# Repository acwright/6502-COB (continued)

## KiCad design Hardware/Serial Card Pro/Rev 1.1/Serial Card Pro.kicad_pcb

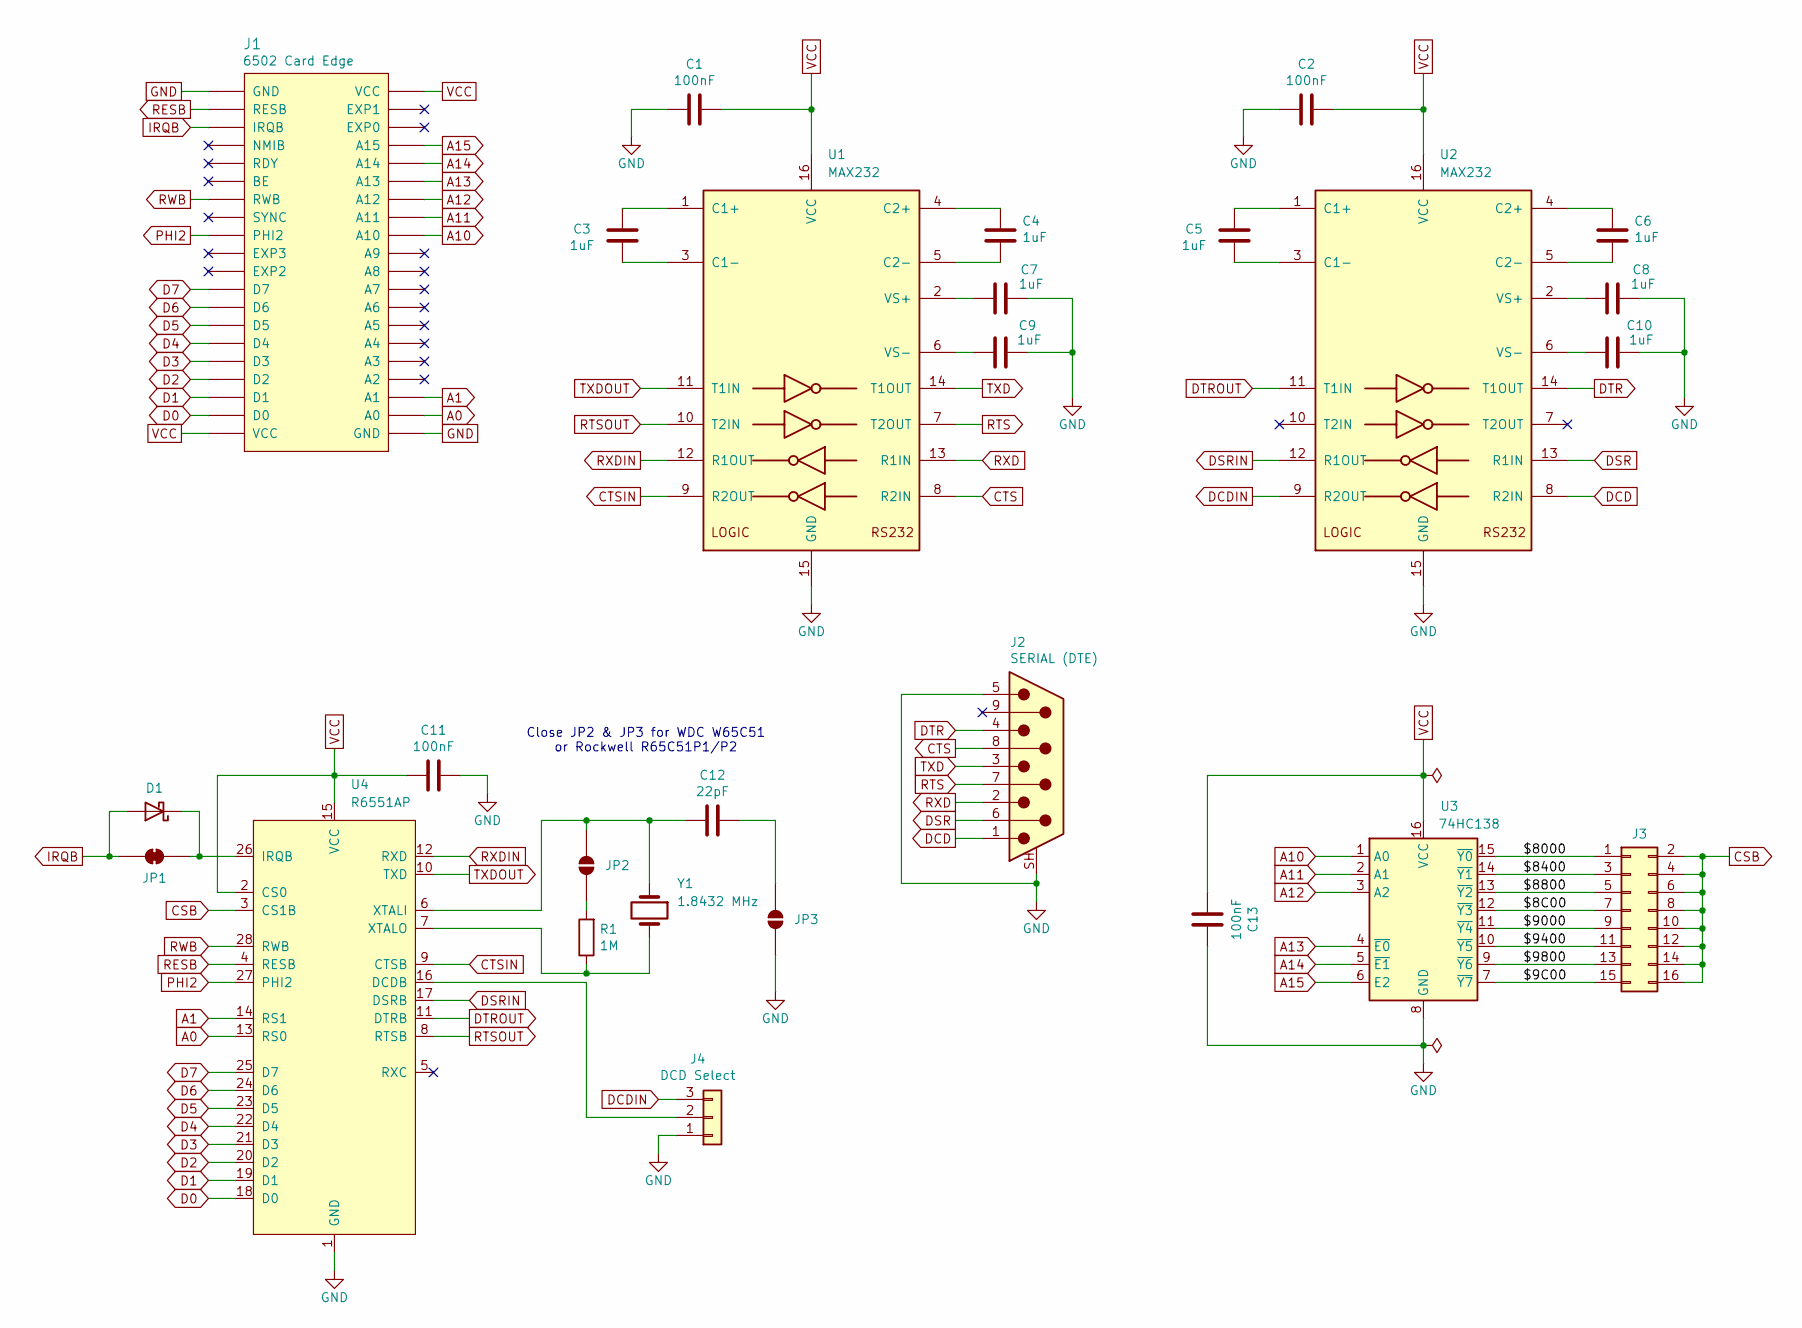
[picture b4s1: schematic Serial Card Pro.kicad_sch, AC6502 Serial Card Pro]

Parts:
C1, C2, C11, C13: 100nF; C_0805_2012Metric; LCSC C49678
C3, C4, C5, C6, C7, C8, C9, C10: 1uF; C_0805_2012Metric; LCSC C28323
C12: 22pF; C_0805_2012Metric; LCSC C1804
D1: BAT85; D_DO-35_SOD27_P7.62mm_Horizontal; Digikey BAT85SCT-ND
J1: 6502 Card Edge
J2: SERIAL (DTE); DSUB-9_Pins_Horizontal_P2.77x2.84mm_EdgePinOffset7.70mm_Hou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; Digikey 609-1481-ND
J3: Conn_02x08_Odd_Even; PinHeader_2x08_P2.54mm_Vertical; Digikey S2011EC-40-ND
J4: DCD Select; PinHeader_1x03_P2.54mm_Vertical; Digikey S1011EC-40-ND
JP1: SolderJumper_2_Bridged; SolderJumper-2_P1.3mm_Bridged_RoundedPad1.0x1.5mm
JP2, JP3: SolderJumper_2_Open; SolderJumper-2_P1.3mm_Open_RoundedPad1.0x1.5mm
R1: 1M; R_0805_2012Metric; LCSC C17514
U1, U2: MAX232; SOIC-16; LCSC C59824
U3: 74HC138; SOIC-16_3.9x9.9mm_P1.27mm; LCSC C5602
U4: R6551AP; DIP-28_W15.24mm_Socket_LongPads
Y1: 1.8432 MHz; Crystal_HC49-U_Vertical; Digikey 535-9009-ND

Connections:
/$8C00: J3.7, U3.12 (~Y3)
/$9C00: J3.15, U3.7 (~Y7)
/$8000: J3.1, U3.15 (~Y0)
/$8400: J3.3, U3.14 (~Y1)
/$8800: J3.5, U3.13 (~Y2)
/$9000: J3.9, U3.11 (~Y4)
/$9400: J3.11, U3.10 (~Y5)
/$9800: J3.13, U3.9 (~Y6)
A0: J1.A0, U4.13 (RS0)
A1: J1.A1, U4.14 (RS1)
A10: J1.A10, U3.1 (A0)
A11: J1.A11, U3.2 (A1)
A12: J1.A12, U3.3 (A2)
A13: J1.A13, U3.4 (~E0)
A14: J1.A14, U3.5 (~E1)
A15: J1.A15, U3.6 (E2)
CSB: J3.2, J3.4, J3.6, J3.8, J3.10, J3.12, J3.14, J3.16, U4.3 (CS1B)
CTS: J2.8, U1.8 (R2IN)
CTSIN: U1.9 (R2OUT), U4.9 (CTSB)
D0: J1.D0, U4.18 (D0)
D1: J1.D1, U4.19 (D1)
D2: J1.D2, U4.20 (D2)
D3: J1.D3, U4.21 (D3)
D4: J1.D4, U4.22 (D4)
D5: J1.D5, U4.23 (D5)
D6: J1.D6, U4.24 (D6)
D7: J1.D7, U4.25 (D7)
DCD: J2.1, U2.8 (R2IN)
DCDIN: J4.3, U2.9 (R2OUT)
DSR: J2.6, U2.13 (R1IN)
DSRIN: U2.12 (R1OUT), U4.17 (DSRB)
DTR: J2.4, U2.14 (T1OUT)
DTROUT: U2.11 (T1IN), U4.11 (DTRB)
GND: C1.1, C2.1, C7.2, C8.2, C9.2, C10.2, C11.2, C13.2, J1.GND, J2.5, J2.SH (PAD), J4.1, JP3.1 (A), U1.15 (GND), U2.15 (GND), U3.8 (GND), U4.1 (GND)
IRQB: D1.2 (A), J1.IRQB, JP1.1 (A)
unnamed: D1.1 (K), JP1.2 (B), U4.26 (IRQB)
unnamed: J4.2, U4.16 (DCDB)
unnamed: JP2.1 (A), R1.2
unnamed: C12.2, JP2.2 (B), U4.6 (XTALI), Y1.1
unnamed: C12.1, JP3.2 (B)
unnamed: C3.1, U1.1 (C1+)
unnamed: C3.2, U1.3 (C1-)
unnamed: C4.1, U1.4 (C2+)
unnamed: C4.2, U1.5 (C2-)
unnamed: C7.1, U1.2 (VS+)
unnamed: C9.1, U1.6 (VS-)
unnamed: C5.1, U2.1 (C1+)
unnamed: C5.2, U2.3 (C1-)
unnamed: C6.1, U2.4 (C2+)
unnamed: C6.2, U2.5 (C2-)
unnamed: C8.1, U2.2 (VS+)
unnamed: C10.1, U2.6 (VS-)
unnamed: R1.1, U4.7 (XTALO), Y1.2
PHI2: J1.PHI2, U4.27 (PHI2)
RESB: J1.RESB, U4.4 (RESB)
RTS: J2.7, U1.7 (T2OUT)
RTSOUT: U1.10 (T2IN), U4.8 (RTSB)
RWB: J1.RWB, U4.28 (RWB)
RXD: J2.2, U1.13 (R1IN)
RXDIN: U1.12 (R1OUT), U4.12 (RXD)
TXD: J2.3, U1.14 (T1OUT)
TXDOUT: U1.11 (T1IN), U4.10 (TXD)
VCC: C1.2, C2.2, C11.1, C13.1, J1.VCC, U1.16 (VCC), U2.16 (VCC), U3.16 (VCC), U4.2 (CS0), U4.15 (VCC)

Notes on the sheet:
Close JP2 & JP3 for WDC W65C51 or Rockwell R65C51P1/P2

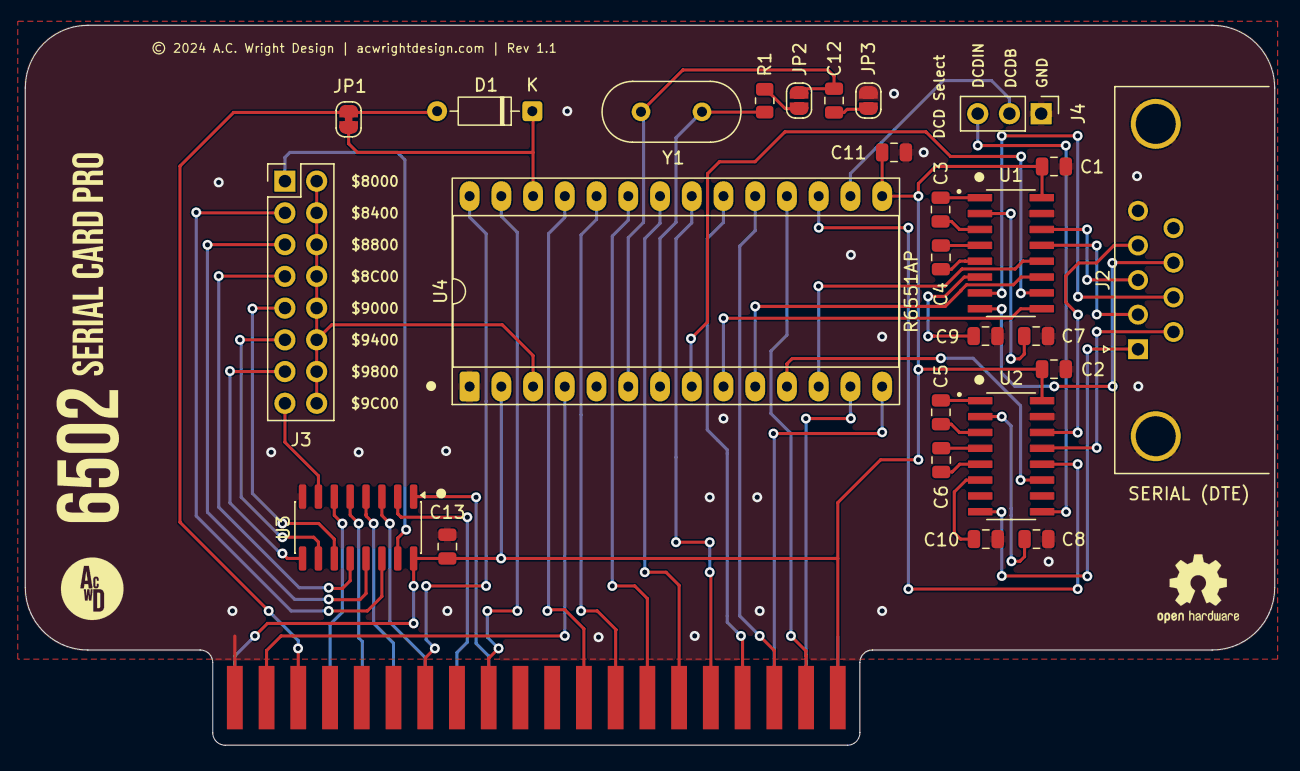
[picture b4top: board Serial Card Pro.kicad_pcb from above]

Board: 2 copper layers, 100.0 x 57.6 mm, 27 parts (0 on the bottom side), 63 nets.

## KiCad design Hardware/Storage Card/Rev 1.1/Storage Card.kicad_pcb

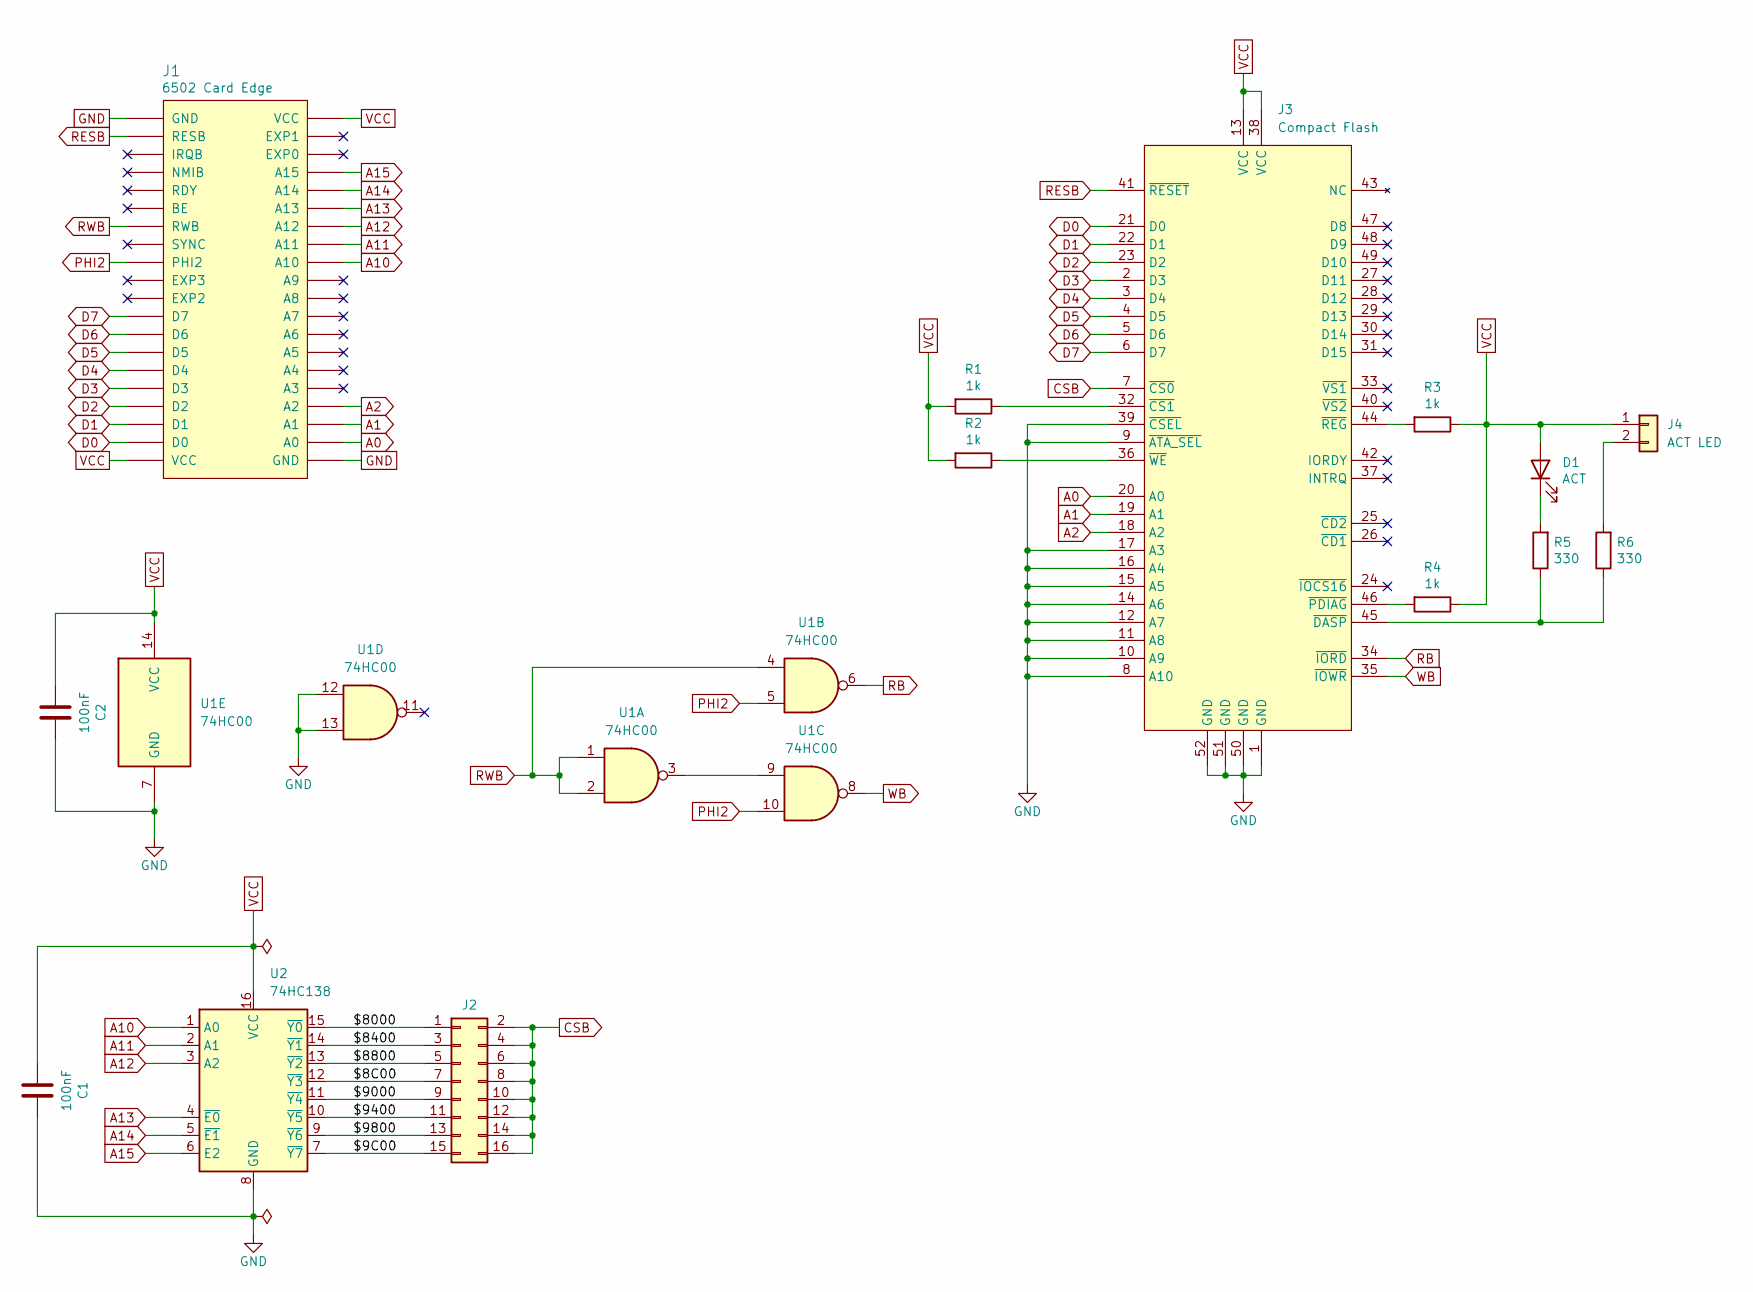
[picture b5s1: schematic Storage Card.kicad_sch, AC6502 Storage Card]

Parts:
C1, C2: 100nF; C_0805_2012Metric; LCSC C49678
D1: ACT; LED_0805_2012Metric; LCSC C2297
J1: 6502 Card Edge
J2: Conn_02x08_Odd_Even; PinHeader_2x08_P2.54mm_Vertical; Digikey S2011EC-40-ND
J3: Compact Flash; CompactFlash Socket Plated Pegs; LCSC C444350
J4: ACT LED; JST_XH_B2B-XH-A_1x02_P2.50mm_Vertical; Digikey 455-B2B-XH-A-ND
R1, R2, R3, R4: 1k; R_0805_2012Metric; LCSC C17513
R5, R6: 330; R_0805_2012Metric; LCSC C17630
U1: 74HC00; SOIC-14_3.9x8.7mm_P1.27mm; LCSC C5586
U2: 74HC138; SOIC-16_3.9x9.9mm_P1.27mm; LCSC C5602

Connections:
/$8C00: J2.7, U2.12 (~Y3)
/$9C00: J2.15, U2.7 (~Y7)
/$8000: J2.1, U2.15 (~Y0)
/$8400: J2.3, U2.14 (~Y1)
/$8800: J2.5, U2.13 (~Y2)
/$9000: J2.9, U2.11 (~Y4)
/$9400: J2.11, U2.10 (~Y5)
/$9800: J2.13, U2.9 (~Y6)
A0: J1.A0, J3.20 (A0)
A1: J1.A1, J3.19 (A1)
A2: J1.A2, J3.18 (A2)
A10: J1.A10, U2.1 (A0)
A11: J1.A11, U2.2 (A1)
A12: J1.A12, U2.3 (A2)
A13: J1.A13, U2.4 (~E0)
A14: J1.A14, U2.5 (~E1)
A15: J1.A15, U2.6 (E2)
CSB: J2.2, J2.4, J2.6, J2.8, J2.10, J2.12, J2.14, J2.16, J3.7 (~CS0)
D0: J1.D0, J3.21 (D0)
D1: J1.D1, J3.22 (D1)
D2: J1.D2, J3.23 (D2)
D3: J1.D3, J3.2 (D3)
D4: J1.D4, J3.3 (D4)
D5: J1.D5, J3.4 (D5)
D6: J1.D6, J3.5 (D6)
D7: J1.D7, J3.6 (D7)
GND: C1.2, C2.2, J1.GND, J3.1 (GND), J3.8 (A10), J3.9 (~ATA_SEL), J3.10 (A9), J3.11 (A8), J3.12 (A7), J3.14 (A6), J3.15 (A5), J3.16 (A4), J3.17 (A3), J3.39 (~CSEL), J3.50 (GND), J3.51 (GND), J3.52 (GND), U1.7 (GND), U1.12, U1.13, U2.8 (GND)
unnamed: D1.1 (K), R5.2
unnamed: J3.32 (~CS1), R1.1
unnamed: J3.45 (~DASP), R5.1, R6.1
unnamed: J3.46 (~PDIAG), R4.2
unnamed: J3.44 (~REG), R3.2
unnamed: J3.36 (~WE), R2.1
unnamed: J4.2, R6.2
unnamed: U1.3, U1.9
PHI2: J1.PHI2, U1.5, U1.10
RB: J3.34 (~IORD), U1.6
RESB: J1.RESB, J3.41 (~RESET)
RWB: J1.RWB, U1.1, U1.2, U1.4
VCC: C1.1, C2.1, D1.2 (A), J1.VCC, J3.13 (VCC), J3.38 (VCC), J4.1, R1.2, R2.2, R3.1, R4.1, U1.14 (VCC), U2.16 (VCC)
WB: J3.35 (~IOWR), U1.8

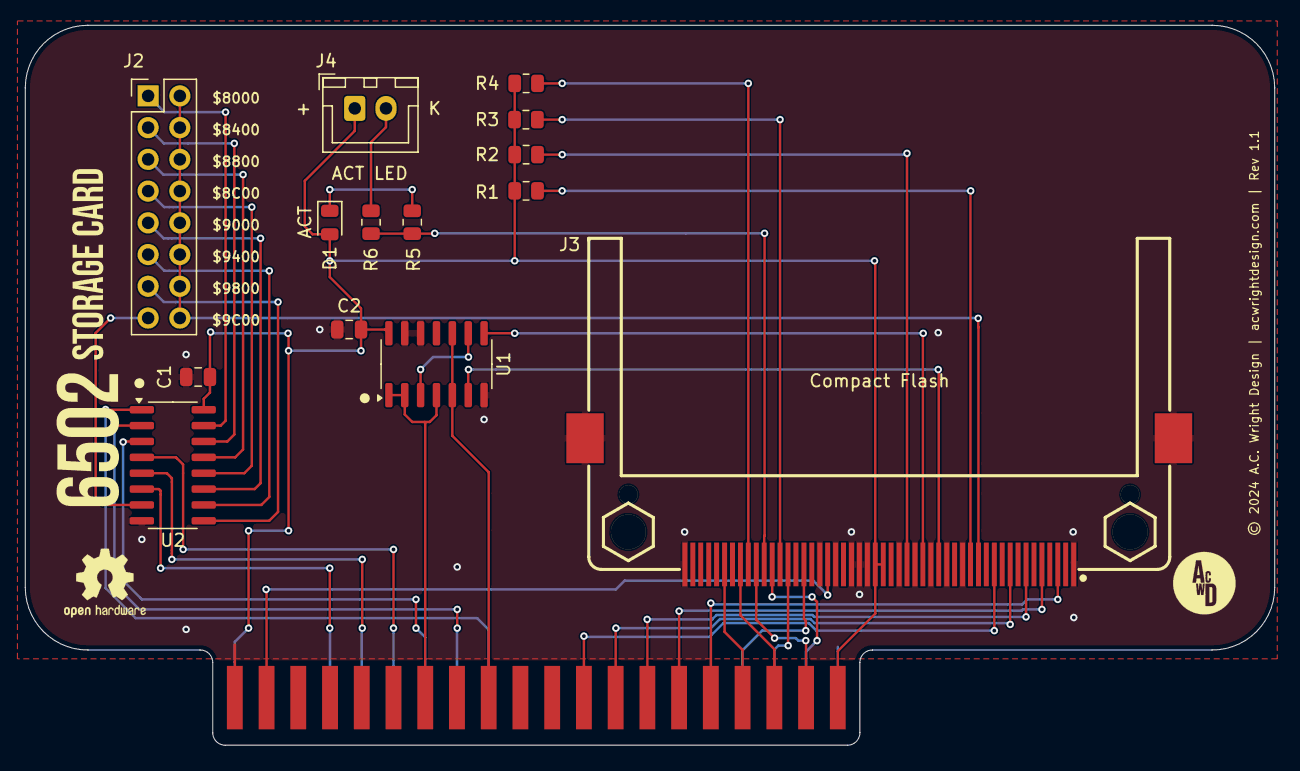
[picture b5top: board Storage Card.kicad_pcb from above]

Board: 2 copper layers, 100.0 x 57.6 mm, 15 parts (0 on the bottom side), 41 nets.

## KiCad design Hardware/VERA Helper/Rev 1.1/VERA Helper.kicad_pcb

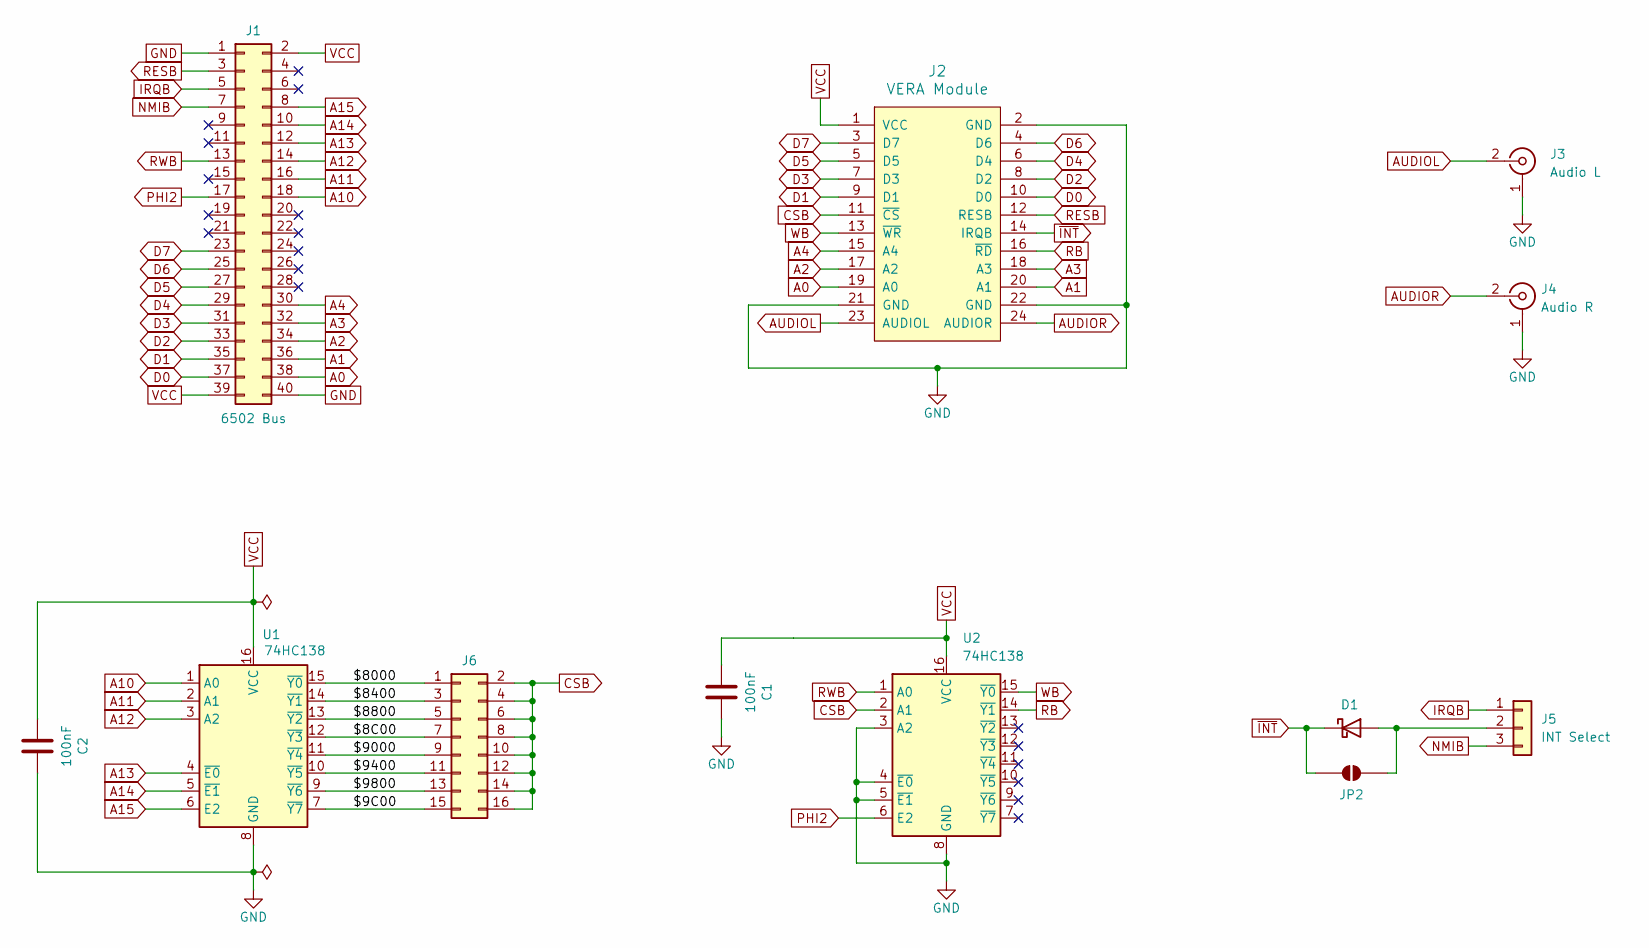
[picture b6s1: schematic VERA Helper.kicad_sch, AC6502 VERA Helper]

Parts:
C1, C2: 100nF; C_Disc_D5.0mm_W2.5mm_P2.50mm; Digikey 478-3187-ND
D1: BAT85; D_DO-35_SOD27_P7.62mm_Horizontal; Digikey BAT85SCT-ND
J1: 6502 Bus; 6502 Bus Connector; Digikey 732-5401-ND
J2: VERA Module; PinHeader_2x12_P2.54mm_Vertical; Digikey S2011EC-40-ND
J3: Audio L; RCA Jack White; Digikey PJRAN1X1U02X-ND
J4: Audio R; RCA Jack White; Digikey PJRAN1X1U03X-ND
J5: INT Select; PinHeader_1x03_P2.54mm_Vertical; Digikey S1011EC-40-ND
J6: Conn_02x08_Odd_Even; PinHeader_2x08_P2.54mm_Vertical; Digikey S2011EC-40-ND
JP2: SolderJumper_2_Open; SolderJumper-2_P1.3mm_Open_RoundedPad1.0x1.5mm
U1, U2: 74HC138; DIP-16_W7.62mm_Socket_LongPads; Digikey 296-1575-5-ND

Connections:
/$8C00: J6.7, U1.12 (~Y3)
/$9C00: J6.15, U1.7 (~Y7)
/$8000: J6.1, U1.15 (~Y0)
/$8400: J6.3, U1.14 (~Y1)
/$8800: J6.5, U1.13 (~Y2)
/$9000: J6.9, U1.11 (~Y4)
/$9400: J6.11, U1.10 (~Y5)
/$9800: J6.13, U1.9 (~Y6)
A0: J1.38, J2.19 (A0)
A1: J1.36, J2.20 (A1)
A2: J1.34, J2.17 (A2)
A3: J1.32, J2.18 (A3)
A4: J1.30, J2.15 (A4)
A10: J1.18, U1.1 (A0)
A11: J1.16, U1.2 (A1)
A12: J1.14, U1.3 (A2)
A13: J1.12, U1.4 (~E0)
A14: J1.10, U1.5 (~E1)
A15: J1.8, U1.6 (E2)
AUDIOL: J2.23 (AUDIOL), J3.2 (In)
AUDIOR: J2.24 (AUDIOR), J4.2 (In)
CSB: J2.11 (~CS), J6.2, J6.4, J6.6, J6.8, J6.10, J6.12, J6.14, J6.16, U2.2 (A1)
D0: J1.37, J2.10 (D0)
D1: J1.35, J2.9 (D1)
D2: J1.33, J2.8 (D2)
D3: J1.31, J2.7 (D3)
D4: J1.29, J2.6 (D4)
D5: J1.27, J2.5 (D5)
D6: J1.25, J2.4 (D6)
D7: J1.23, J2.3 (D7)
GND: C1.2, C2.2, J1.1, J1.40, J2.2 (GND), J2.21 (GND), J2.22 (GND), J3.1 (Ext), J4.1 (Ext), U1.8 (GND), U2.3 (A2), U2.4 (~E0), U2.5 (~E1), U2.8 (GND)
IRQB: J1.5, J5.1
NMIB: J1.7, J5.3
unnamed: D1.2 (A), J5.2, JP2.2 (B)
PHI2: J1.17, U2.6 (E2)
RB: J2.16 (~RD), U2.14 (~Y1)
RESB: J1.3, J2.12 (RESB)
RWB: J1.13, U2.1 (A0)
VCC: C1.1, C2.1, J1.2, J1.39, J2.1 (VCC), U1.16 (VCC), U2.16 (VCC)
WB: J2.13 (~WR), U2.15 (~Y0)
~INT: D1.1 (K), J2.14 (IRQB), JP2.1 (A)

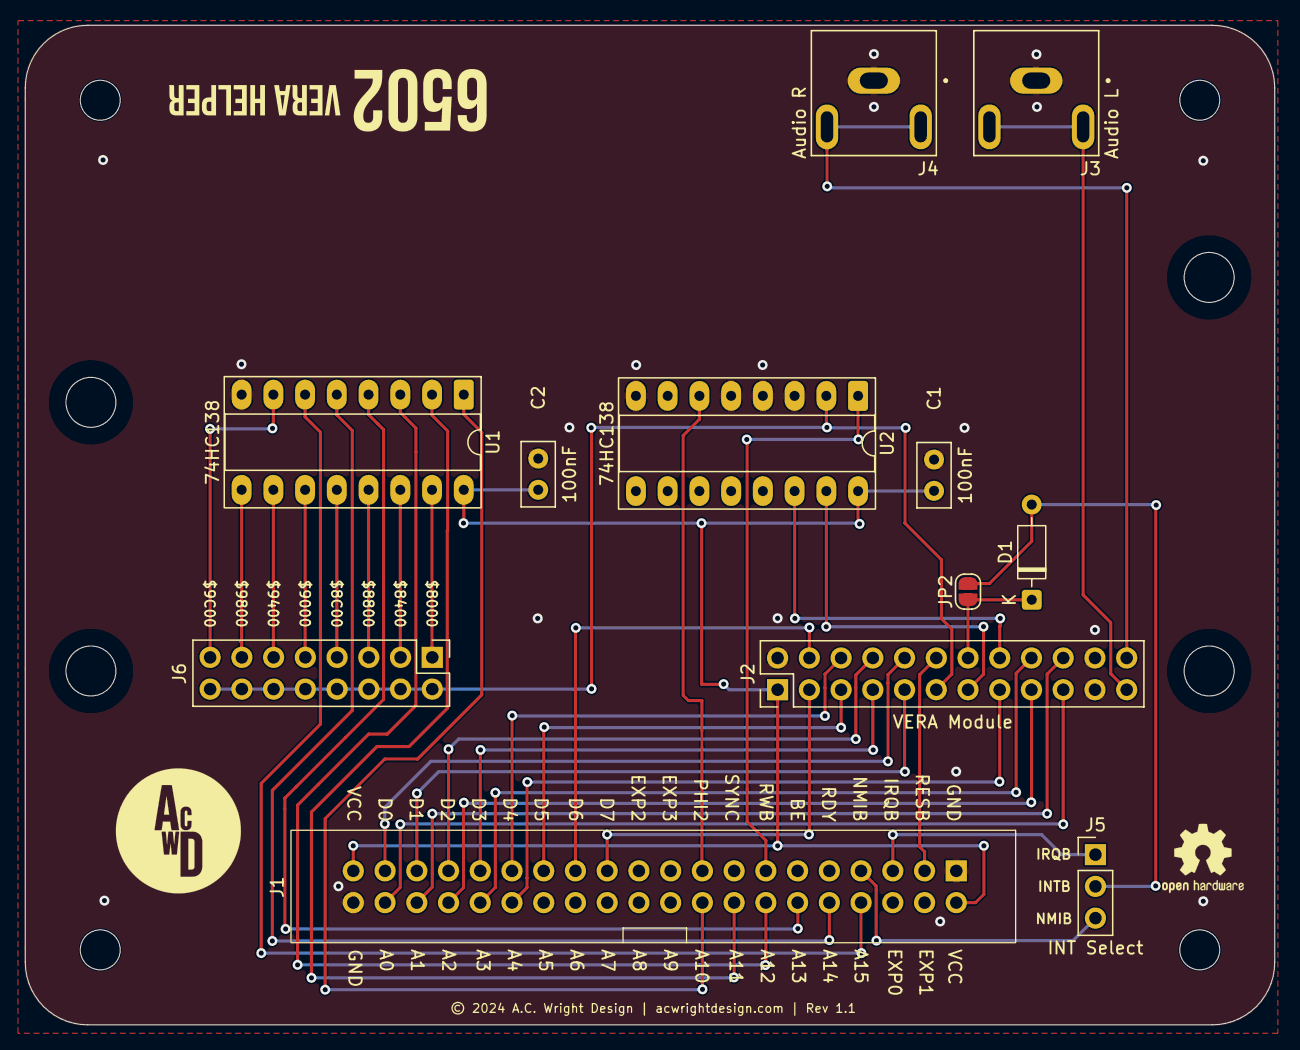
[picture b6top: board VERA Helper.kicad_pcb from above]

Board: 2 copper layers, 100.0 x 80.0 mm, 16 parts (0 on the bottom side), 41 nets.

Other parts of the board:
H1, H2, H3, H4: MountingHole; MountingHole_3.2mm_M3

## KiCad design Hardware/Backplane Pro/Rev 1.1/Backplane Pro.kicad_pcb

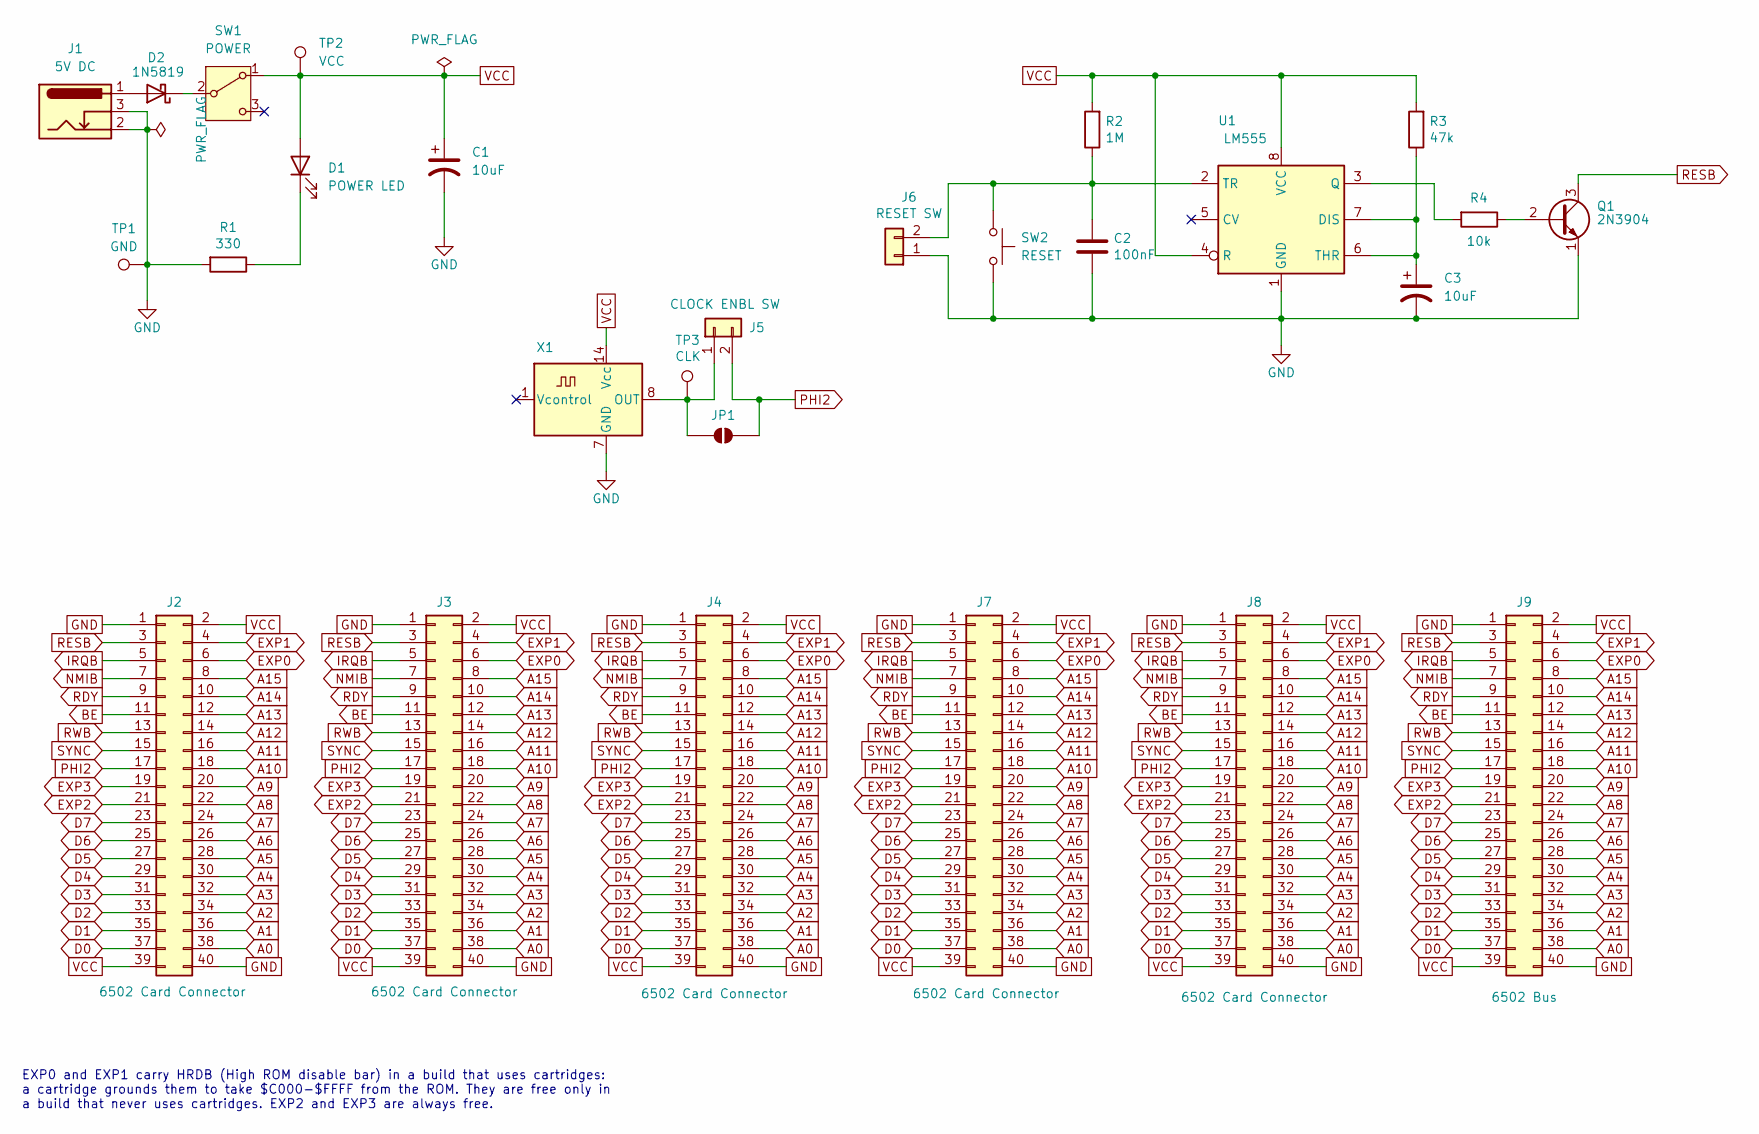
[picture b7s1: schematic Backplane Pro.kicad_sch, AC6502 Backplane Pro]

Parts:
C1, C3: 10uF; CP_Radial_D4.0mm_P1.50mm; Digikey P14482-ND
C2: 100nF; C_Disc_D5.0mm_W2.5mm_P2.50mm; Digikey 478-3187-ND
D1: POWER LED; LED_D3.0mm; Digikey 732-5008-ND
D2: 1N5819; D_DO-41_SOD81_P10.16mm_Horizontal; Digikey 1N5819-E3/54GICT-ND
J1: 5V DC; BarrelJack_Horizontal; Digikey CP-102AH-ND
J2, J3, J4, J7, J8: 6502 Card Connector; 6502 Card Slot; Mouser 571-5-5530843-4
J5: CLOCK ENBL SW; JST_XH_B2B-XH-A_1x02_P2.50mm_Vertical; Digikey 455-B2B-XH-A-ND
J6: RESET SW; JST_XH_B2B-XH-A_1x02_P2.50mm_Vertical; Digikey 455-B2B-XH-A-ND
J9: 6502 Bus; 6502 Bus Connector; Digikey 732-5401-ND
JP1: SolderJumper_2_Open; SolderJumper-2_P1.3mm_Open_RoundedPad1.0x1.5mm
Q1: 2N3904; TO-92_Inline; Digikey 2N3904FS-ND
R1: 330; R_Axial_DIN0204_L3.6mm_D1.6mm_P5.08mm_Horizontal; Digikey 13-MFR-12FTF52-330RCT-ND
R2: 1M; R_Axial_DIN0204_L3.6mm_D1.6mm_P5.08mm_Horizontal; Digikey 13-MFR-12FTF52-1MCT-ND
R3: 47k; R_Axial_DIN0204_L3.6mm_D1.6mm_P5.08mm_Horizontal; Digikey 13-MFR-12FTF52-47KCT-ND
R4: 10k; R_Axial_DIN0204_L3.6mm_D1.6mm_P5.08mm_Horizontal; Digikey 13-MFR-12FTF52-10KCT-ND
SW1: POWER; Power Switch; Digikey EG4326-ND
SW2: RESET; SW_PUSH_6mm; Digikey 2223-TS02-66-50-BK-160-LCR-D-ND
TP1: GND; TestPoint_Pad_2.5x2.5mm
TP2: VCC; TestPoint_Pad_2.5x2.5mm
TP3: CLK; TestPoint_Pad_1.0x1.0mm
U1: LM555; DIP-8_W7.62mm_Socket_LongPads; Digikey LM555CNNS/NOPB-ND
X1: 1 MHz; Oscillator_DIP-14; Digikey X937-ND

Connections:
A0: J2.38, J3.38, J4.38, J7.38, J8.38, J9.38
A1: J2.36, J3.36, J4.36, J7.36, J8.36, J9.36
A2: J2.34, J3.34, J4.34, J7.34, J8.34, J9.34
A3: J2.32, J3.32, J4.32, J7.32, J8.32, J9.32
A4: J2.30, J3.30, J4.30, J7.30, J8.30, J9.30
A5: J2.28, J3.28, J4.28, J7.28, J8.28, J9.28
A6: J2.26, J3.26, J4.26, J7.26, J8.26, J9.26
A7: J2.24, J3.24, J4.24, J7.24, J8.24, J9.24
A8: J2.22, J3.22, J4.22, J7.22, J8.22, J9.22
A9: J2.20, J3.20, J4.20, J7.20, J8.20, J9.20
A10: J2.18, J3.18, J4.18, J7.18, J8.18, J9.18
A11: J2.16, J3.16, J4.16, J7.16, J8.16, J9.16
A12: J2.14, J3.14, J4.14, J7.14, J8.14, J9.14
A13: J2.12, J3.12, J4.12, J7.12, J8.12, J9.12
A14: J2.10, J3.10, J4.10, J7.10, J8.10, J9.10
A15: J2.8, J3.8, J4.8, J7.8, J8.8, J9.8
BE: J2.11, J3.11, J4.11, J7.11, J8.11, J9.11
D0: J2.37, J3.37, J4.37, J7.37, J8.37, J9.37
D1: J2.35, J3.35, J4.35, J7.35, J8.35, J9.35
D2: J2.33, J3.33, J4.33, J7.33, J8.33, J9.33
D3: J2.31, J3.31, J4.31, J7.31, J8.31, J9.31
D4: J2.29, J3.29, J4.29, J7.29, J8.29, J9.29
D5: J2.27, J3.27, J4.27, J7.27, J8.27, J9.27
D6: J2.25, J3.25, J4.25, J7.25, J8.25, J9.25
D7: J2.23, J3.23, J4.23, J7.23, J8.23, J9.23
EXP0: J2.6, J3.6, J4.6, J7.6, J8.6, J9.6
EXP1: J2.4, J3.4, J4.4, J7.4, J8.4, J9.4
EXP2: J2.21, J3.21, J4.21, J7.21, J8.21, J9.21
EXP3: J2.19, J3.19, J4.19, J7.19, J8.19, J9.19
GND: C1.2, C2.2, C3.2, J1.2, J1.3, J2.1, J2.40, J3.1, J3.40, J4.1, J4.40, J6.1, J7.1, J7.40, J8.1, J8.40, J9.1, J9.40, Q1.1 (E), R1.2, SW2.2, TP1.1 (1_1), U1.1 (GND), X1.7 (GND)
IRQB: J2.5, J3.5, J4.5, J7.5, J8.5, J9.5
NMIB: J2.7, J3.7, J4.7, J7.7, J8.7, J9.7
unnamed: D1.1 (K), R1.1
unnamed: D2.2 (A), J1.1
unnamed: D2.1 (K), SW1.2 (B)
unnamed: J5.1, JP1.1 (A), TP3.1 (1_1), X1.8 (OUT)
unnamed: C2.1, J6.2, R2.1, SW2.1, U1.2 (TR)
unnamed: Q1.2 (B), R4.1
unnamed: C3.1, R3.1, U1.6 (THR), U1.7 (DIS)
unnamed: R4.2, U1.3 (Q)
PHI2: J2.17, J3.17, J4.17, J5.2, J7.17, J8.17, J9.17, JP1.2 (B)
RDY: J2.9, J3.9, J4.9, J7.9, J8.9, J9.9
RESB: J2.3, J3.3, J4.3, J7.3, J8.3, J9.3, Q1.3 (C)
RWB: J2.13, J3.13, J4.13, J7.13, J8.13, J9.13
SYNC: J2.15, J3.15, J4.15, J7.15, J8.15, J9.15
VCC: C1.1, D1.2 (A), J2.2, J2.39, J3.2, J3.39, J4.2, J4.39, J7.2, J7.39, J8.2, J8.39, J9.2, J9.39, R2.2, R3.2, SW1.1 (A), TP2.1 (1_1), U1.4 (R), U1.8 (VCC), X1.14 (Vcc)

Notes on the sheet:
EXP0 and EXP1 carry HRDB (High ROM disable bar) in a build that uses cartridges: a cartridge grounds them to take $C000-$FFFF from the ROM. They are free only in a build that never uses cartridges. EXP2 and EXP3 are always free.

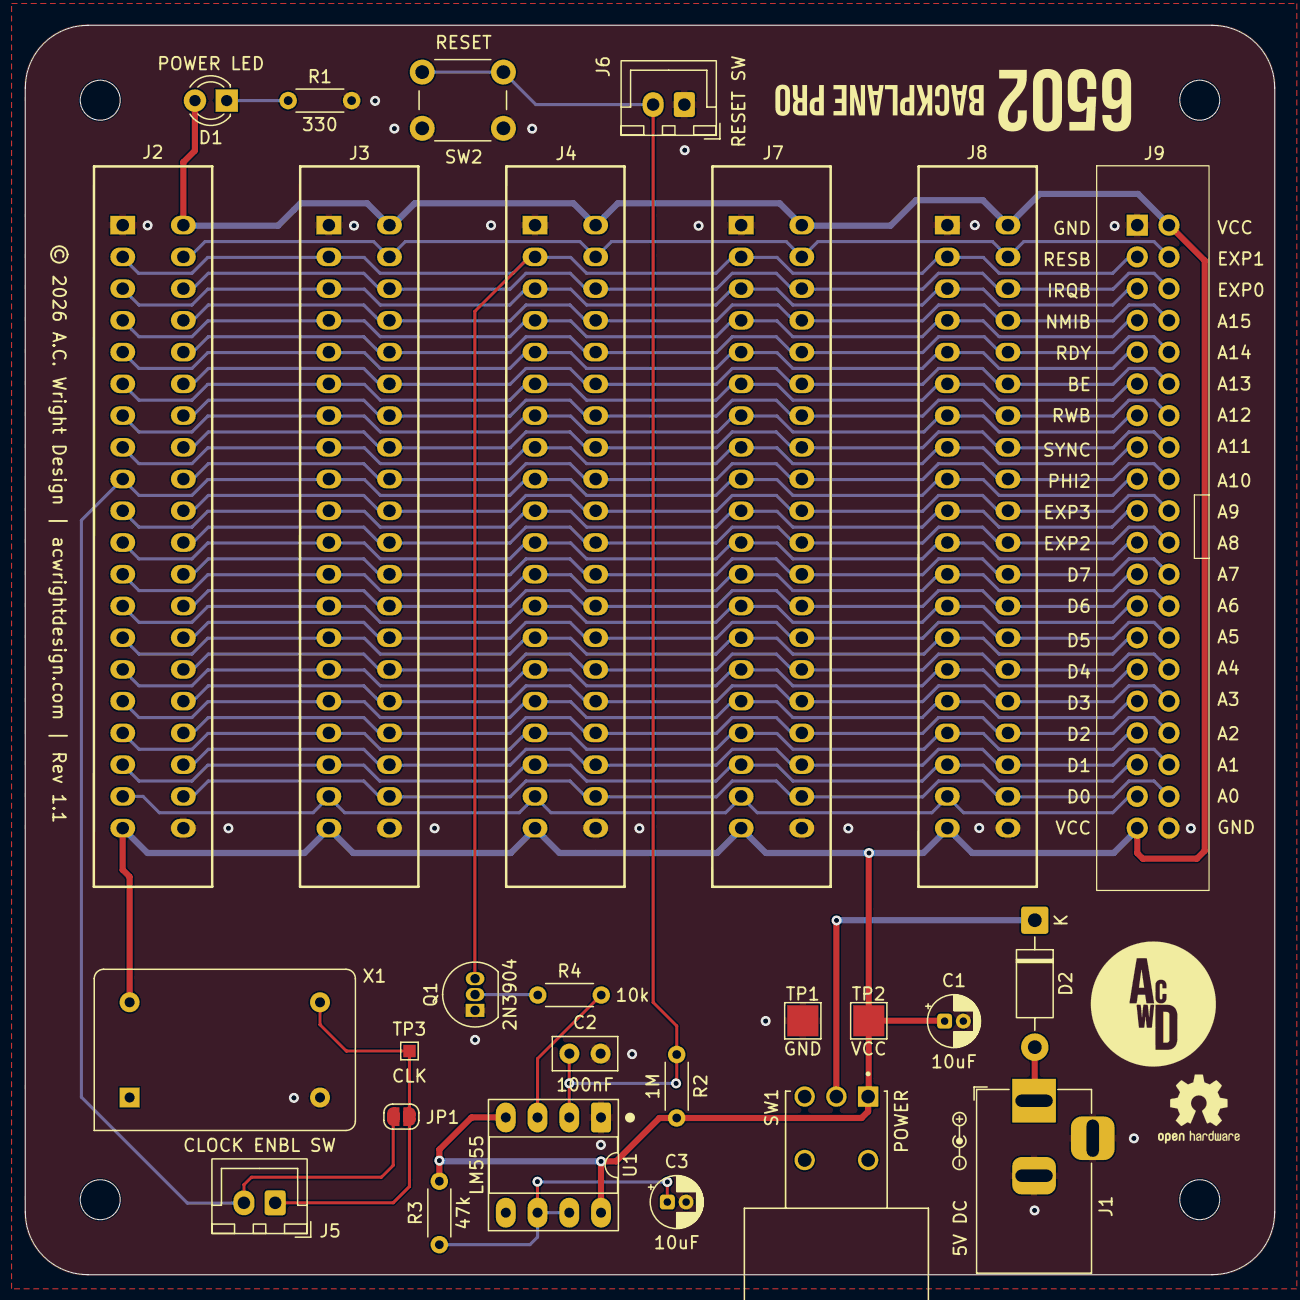
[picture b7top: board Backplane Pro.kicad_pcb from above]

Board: 2 copper layers, 100.0 x 100.0 mm, 31 parts (0 on the bottom side), 46 nets.

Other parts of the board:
H1, H2, H3, H4: MountingHole; MountingHole_3.2mm_M3

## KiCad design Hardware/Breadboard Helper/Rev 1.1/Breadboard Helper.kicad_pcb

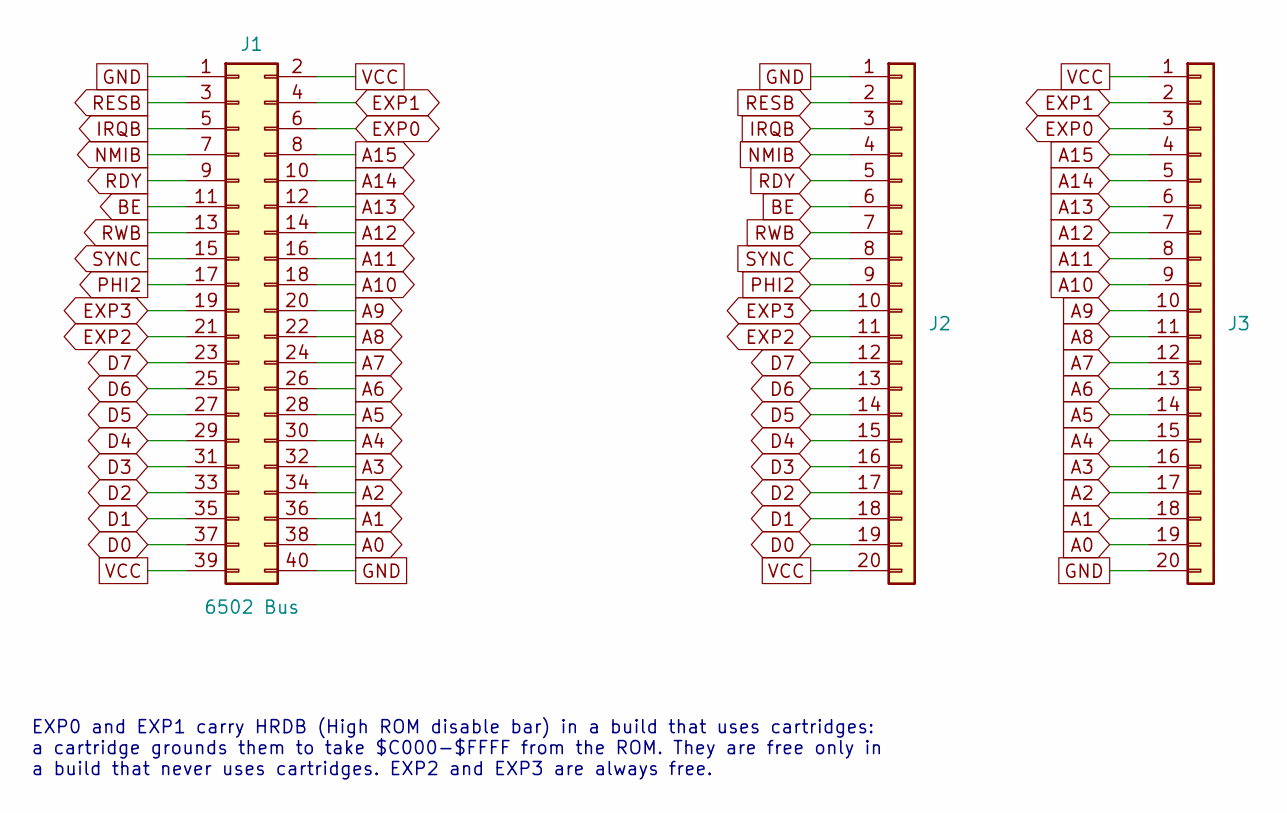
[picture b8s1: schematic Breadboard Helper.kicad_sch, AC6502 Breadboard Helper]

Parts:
J1: 6502 Bus; 6502 Bus Connector; Digikey 732-5401-ND
J2, J3: Conn_01x20; PinHeader_1x20_P2.54mm_Vertical; Digikey S1011EC-40-ND

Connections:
A0: J1.38, J3.19
A1: J1.36, J3.18
A2: J1.34, J3.17
A3: J1.32, J3.16
A4: J1.30, J3.15
A5: J1.28, J3.14
A6: J1.26, J3.13
A7: J1.24, J3.12
A8: J1.22, J3.11
A9: J1.20, J3.10
A10: J1.18, J3.9
A11: J1.16, J3.8
A12: J1.14, J3.7
A13: J1.12, J3.6
A14: J1.10, J3.5
A15: J1.8, J3.4
BE: J1.11, J2.6
D0: J1.37, J2.19
D1: J1.35, J2.18
D2: J1.33, J2.17
D3: J1.31, J2.16
D4: J1.29, J2.15
D5: J1.27, J2.14
D6: J1.25, J2.13
D7: J1.23, J2.12
EXP0: J1.6, J3.3
EXP1: J1.4, J3.2
EXP2: J1.21, J2.11
EXP3: J1.19, J2.10
GND: J1.1, J1.40, J2.1, J3.20
IRQB: J1.5, J2.3
NMIB: J1.7, J2.4
PHI2: J1.17, J2.9
RDY: J1.9, J2.5
RESB: J1.3, J2.2
RWB: J1.13, J2.7
SYNC: J1.15, J2.8
VCC: J1.2, J1.39, J2.20, J3.1

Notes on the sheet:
EXP0 and EXP1 carry HRDB (High ROM disable bar) in a build that uses cartridges: a cartridge grounds them to take $C000-$FFFF from the ROM. They are free only in a build that never uses cartridges. EXP2 and EXP3 are always free.
